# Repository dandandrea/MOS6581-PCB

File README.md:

# MOS6581-PCB
KiCad PCB layouts for MOS6581 synthesizer project

These boards host a _Commodore / MOS Technology **MOS6581** sound synthesis IC_ (see datasheet below).

[Click here for the MOS6581 datasheet](http://archive.6502.org/datasheets/mos_6581_sid.pdf)

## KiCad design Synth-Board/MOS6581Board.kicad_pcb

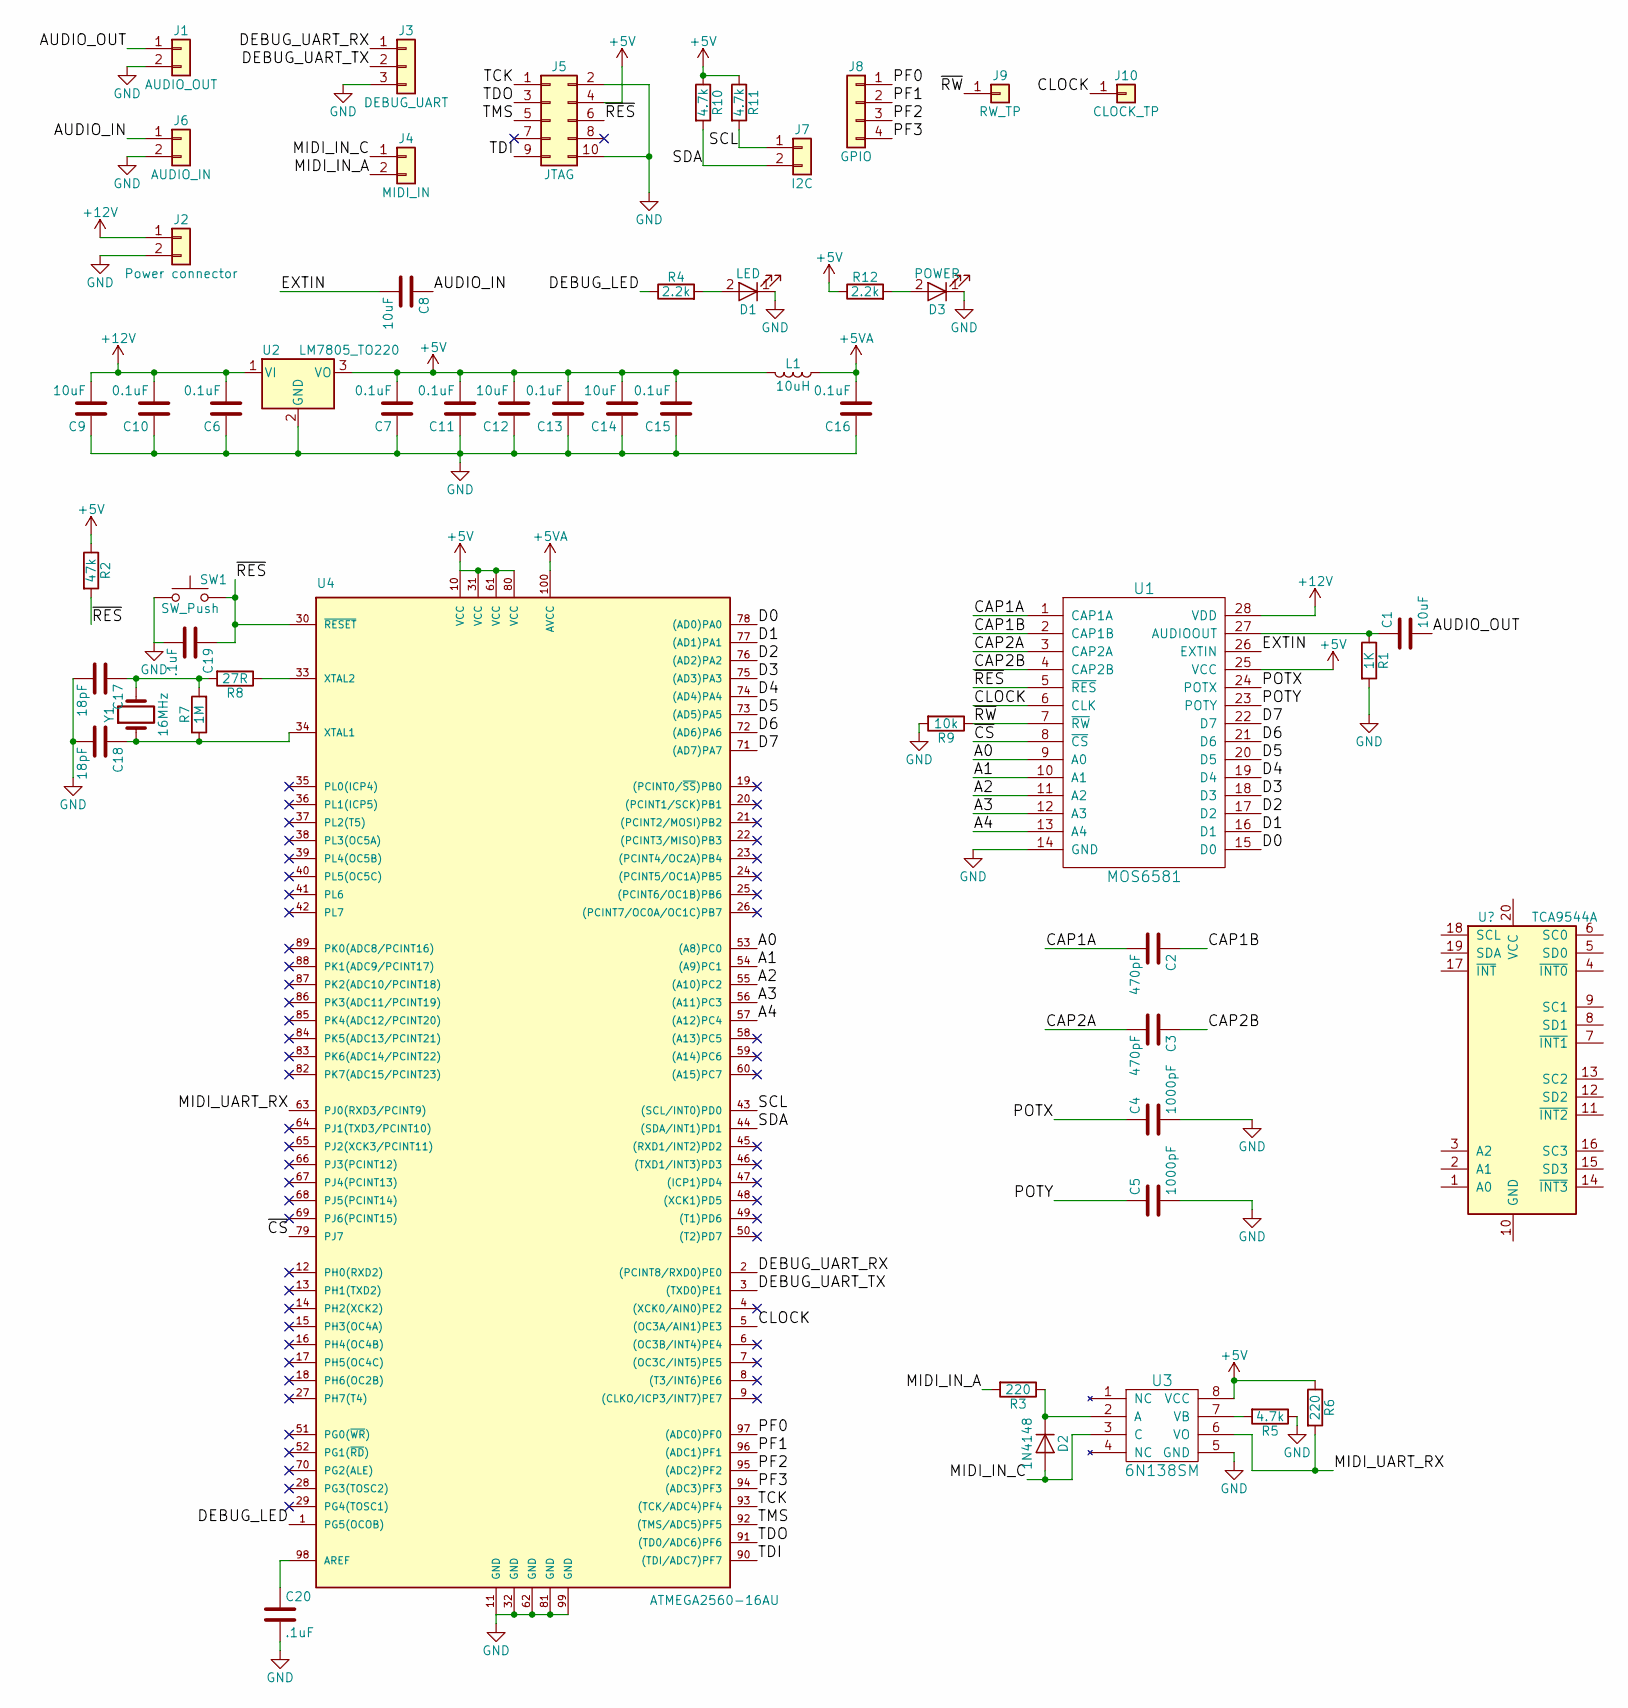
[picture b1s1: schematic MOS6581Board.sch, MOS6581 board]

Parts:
C1, C8: 10uF; CP_Radial_D5.0mm_P2.50mm
C2, C3: 470pF; R_Axial_DIN0614_L14.3mm_D5.7mm_P20.32mm_Horizontal
C4, C5: 1000pF; C_0805_HandSoldering
C6, C7, C10, C11, C13, C15, C16: 0.1uF; C_0805_HandSoldering
C9, C12, C14: 10uF; C_0805_HandSoldering
C17, C18: 18pF; C_0805_HandSoldering
C19, C20: .1uF; C_0805_HandSoldering
D1: LED; LED_0805_HandSoldering
D2: 1N4148; D_SOD-323_HandSoldering
D3: POWER; LED_0805_HandSoldering
J1: AUDIO_OUT; Pin_Header_Straight_1x02_Pitch2.54mm
J2: Power connector; Pin_Header_Straight_1x02_Pitch2.54mm
J3: DEBUG_UART; Pin_Header_Straight_1x03_Pitch2.54mm
J4: MIDI_IN; Pin_Header_Straight_1x02_Pitch2.54mm
J5: JTAG; Pin_Header_Straight_2x05_Pitch2.54mm
J6: AUDIO_IN; Pin_Header_Straight_1x02_Pitch2.54mm
J7: I2C; Pin_Header_Straight_1x02_Pitch2.54mm
J8: GPIO; Pin_Header_Straight_1x04_Pitch1.27mm
J9: RW_TP; Pin_Header_Straight_1x01_Pitch1.27mm
J10: CLOCK_TP; Pin_Header_Straight_1x01_Pitch1.27mm
L1: 10uH; R_1206_HandSoldering
R1: 1K; C_1206
R2: 47k; R_0805_HandSoldering
R3, R6: 220; R_0805_HandSoldering
R4, R12: 2.2k; R_0805_HandSoldering
R5, R10, R11: 4.7k; R_0805_HandSoldering
R7: 1M; R_0805_HandSoldering
R8: 27R; R_0805_HandSoldering
R9: 10k; R_0805_HandSoldering
SW1: SW_Push; SW_PUSH_6mm
U1: MOS6581; DIP-28_W15.24mm_Socket
U2: LM7805_TO220; TO-220-3_Vertical
U3: 6N138SM; SMDIP-8_W7.62mm
U4: ATMEGA2560-16AU; TQFP-100_14x14mm_Pitch0.5mm
Y1: 16MHz; Crystal_SMD_HC49-SD_HandSoldering

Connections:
+5V: C7.2, C11.2, C12.2, C13.2, C14.2, C15.2, J5.4, L1.2, R2.1, R6.1, R10.1, R11.1, R12.1, U1.25 (VCC), U2.3 (VO), U3.8 (VCC), U4.10 (VCC), U4.31 (VCC), U4.61 (VCC), U4.80 (VCC)
+5VA: C16.2, L1.1, U4.100 (AVCC)
+12V: C6.2, C9.2, C10.2, J2.1, U1.28 (VDD), U2.1 (VI)
/A0: U1.9 (A0), U4.53 ((A8)PC0)
/A1: U1.10 (A1), U4.54 ((A9)PC1)
/A2: U1.11 (A2), U4.55 ((A10)PC2)
/A3: U1.12 (A3), U4.56 ((A11)PC3)
/A4: U1.13 (A4), U4.57 ((A12)PC4)
/AUDIO_IN: C8.1, J6.1
/AUDIO_OUT: C1.2, J1.1
/CAP1A: C2.2, U1.1 (CAP1A)
/CAP1B: C2.1, U1.2 (CAP1B)
/CAP2A: C3.2, U1.3 (CAP2A)
/CAP2B: C3.1, U1.4 (CAP2B)
/CLOCK: J10.1, U1.6 (CLK), U4.5 ((OC3A/AIN1)PE3)
/D0: U1.15 (D0), U4.78 ((AD0)PA0)
/D1: U1.16 (D1), U4.77 ((AD1)PA1)
/D2: U1.17 (D2), U4.76 ((AD2)PA2)
/D3: U1.18 (D3), U4.75 ((AD3)PA3)
/D4: U1.19 (D4), U4.74 ((AD4)PA4)
/D5: U1.20 (D5), U4.73 ((AD5)PA5)
/D6: U1.21 (D6), U4.72 ((AD6)PA6)
/D7: U1.22 (D7), U4.71 ((AD7)PA7)
/DEBUG_LED: R4.1, U4.1 (PG5(OCOB))
/DEBUG_UART_RX: J3.1, U4.2 ((PCINT8/RXD0)PE0)
/DEBUG_UART_TX: J3.2, U4.3 ((TXD0)PE1)
/EXTIN: C8.2, U1.26 (EXTIN)
/MIDI_IN_A: J4.2, R3.2
/MIDI_IN_C: D2.2 (A), J4.1, U3.3 (C)
/MIDI_UART_RX: R6.2, U3.6 (VO), U4.63 (PJ0(RXD3/PCINT9))
/PF0: J8.1, U4.97 ((ADC0)PF0)
/PF1: J8.2, U4.96 ((ADC1)PF1)
/PF2: J8.3, U4.95 ((ADC2)PF2)
/PF3: J8.4, U4.94 ((ADC3)PF3)
/POTX: C4.1, U1.24 (POTX)
/POTY: C5.1, U1.23 (POTY)
/SCL: J7.1, R11.2, U4.43 ((SCL/INT0)PD0)
/SDA: J7.2, R10.2, U4.44 ((SDA/INT1)PD1)
/TCK: J5.1, U4.93 ((TCK/ADC4)PF4)
/TDI: J5.9, U4.90 ((TDI/ADC7)PF7)
/TDO: J5.3, U4.91 ((TD0/ADC6)PF6)
/TMS: J5.5, U4.92 ((TMS/ADC5)PF5)
/~CS: U1.8 (~CS), U4.79 (PJ7)
/~RES: C19.1, J5.6, R2.2, SW1.2, U1.5 (~RES), U4.30 (~RESET)
/~RW: J9.1, R9.1, U1.7 (~RW)
GND: C4.2, C5.2, C6.1, C7.1, C9.1, C10.1, C11.1, C12.1, C13.1, C14.1, C15.1, C16.1, C17.2, C18.2, C19.2, C20.2, D1.1 (K), D3.1 (K), J1.2, J2.2, J3.3, J5.2, J5.10, J6.2, R1.2, R5.1, R9.2, SW1.1, U1.14 (GND), U2.2 (GND), U3.5 (GND), U4.11 (GND), U4.32 (GND), U4.62 (GND), U4.81 (GND), U4.99 (GND)
unnamed: C1.1, R1.1, U1.27 (AUDIOOUT)
unnamed: C17.1, R7.2, R8.2, Y1.2
unnamed: C18.1, R7.1, U4.34 (XTAL1), Y1.1
unnamed: C20.1, U4.98 (AREF)
unnamed: D1.2 (A), R4.2
unnamed: D2.1 (K), R3.1, U3.2 (A)
unnamed: D3.2 (A), R12.2
unnamed: R5.2, U3.7 (VB)
unnamed: R8.1, U4.33 (XTAL2)

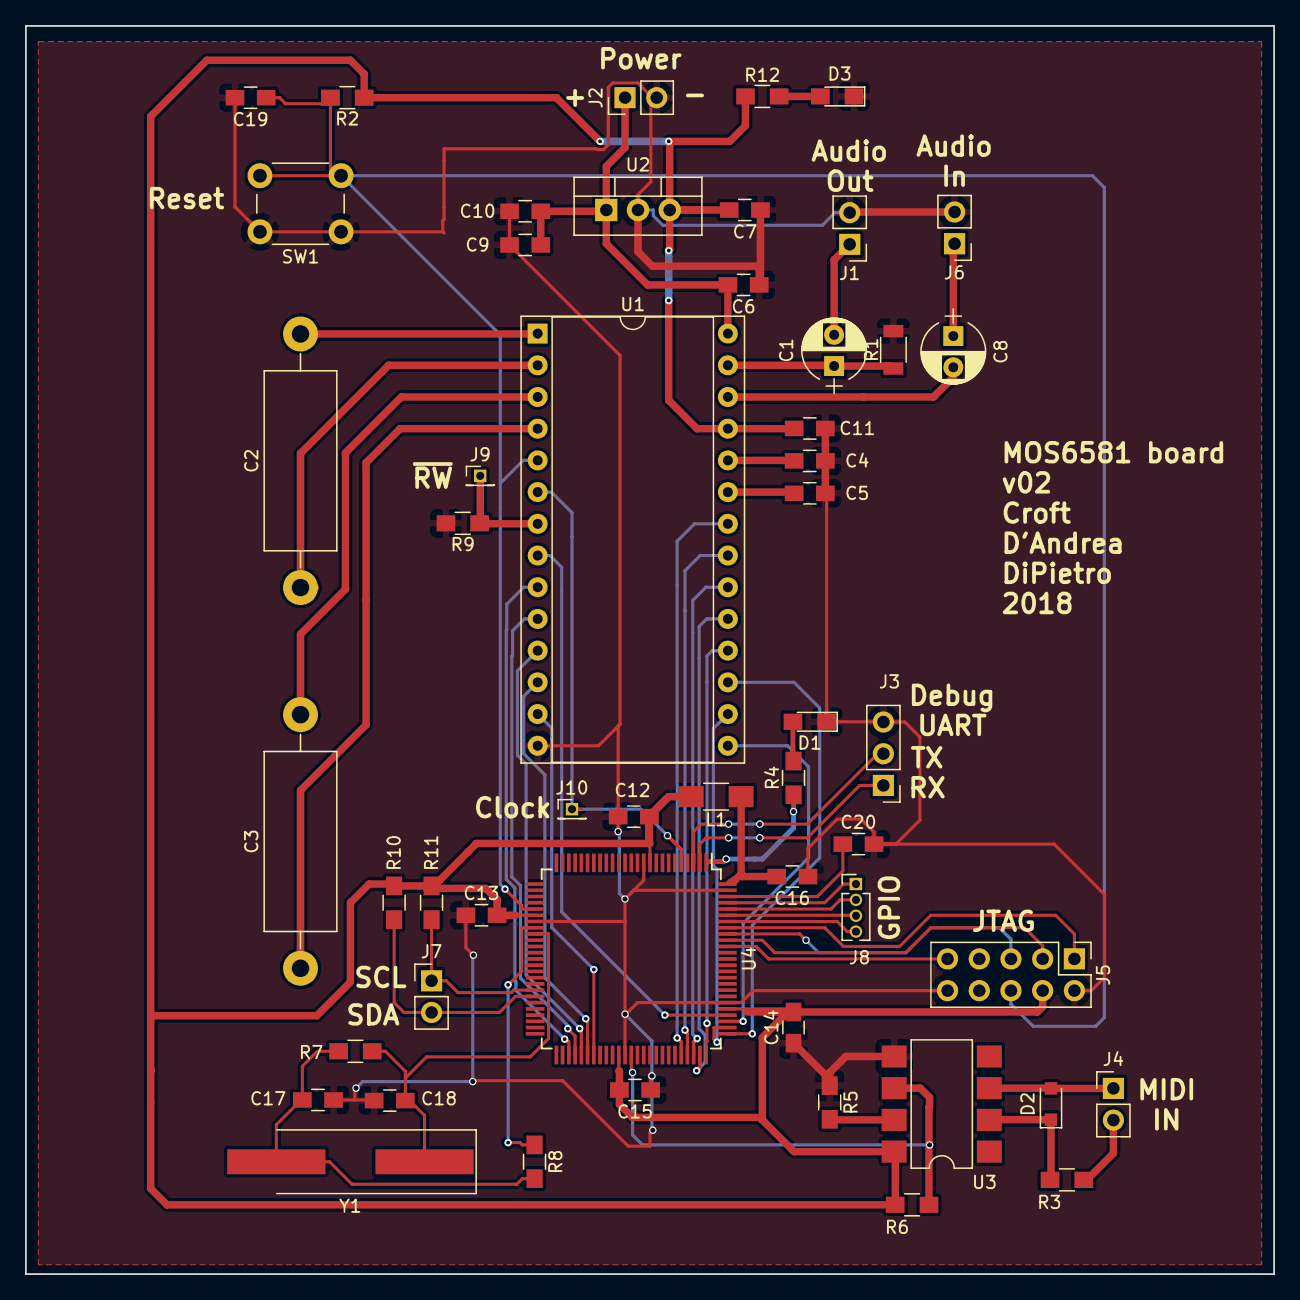
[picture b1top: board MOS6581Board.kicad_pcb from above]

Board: 2 copper layers, 100.0 x 100.0 mm, 52 parts (0 on the bottom side), 55 nets.

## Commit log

2018-11-11 Further flesh out README contents
2018-11-11 Fix very minor detail in README contents
2018-11-11 Fix very minor details in README contents
2018-11-12 Add Netlist & "cache" .lib files to source control
2018-11-14 added missing layers and regenerated gerbers.
2018-12-17 Add latest changes
2018-12-17 laid out general paths for data and address lines.
2018-12-19 Add auto-routed PCB
2018-12-20 Attempt a tighter board layout
2018-12-21 cleaned up layout.
2018-12-21 did a little more cleanup around the crystal oscillator.
2018-12-27 Put various KiCad projects under one Git repo
2018-12-27 laid out schematic for single osc control.
2018-12-28 added i2c address switch to osc board design.
2018-12-29 osc schematic touchup.
2018-12-29 added pullups and caps in various places on osc sch.
2018-12-31 added footprints.
2018-12-31 added i2c mux to synth board.
2020-07-04 not sure what has changed
